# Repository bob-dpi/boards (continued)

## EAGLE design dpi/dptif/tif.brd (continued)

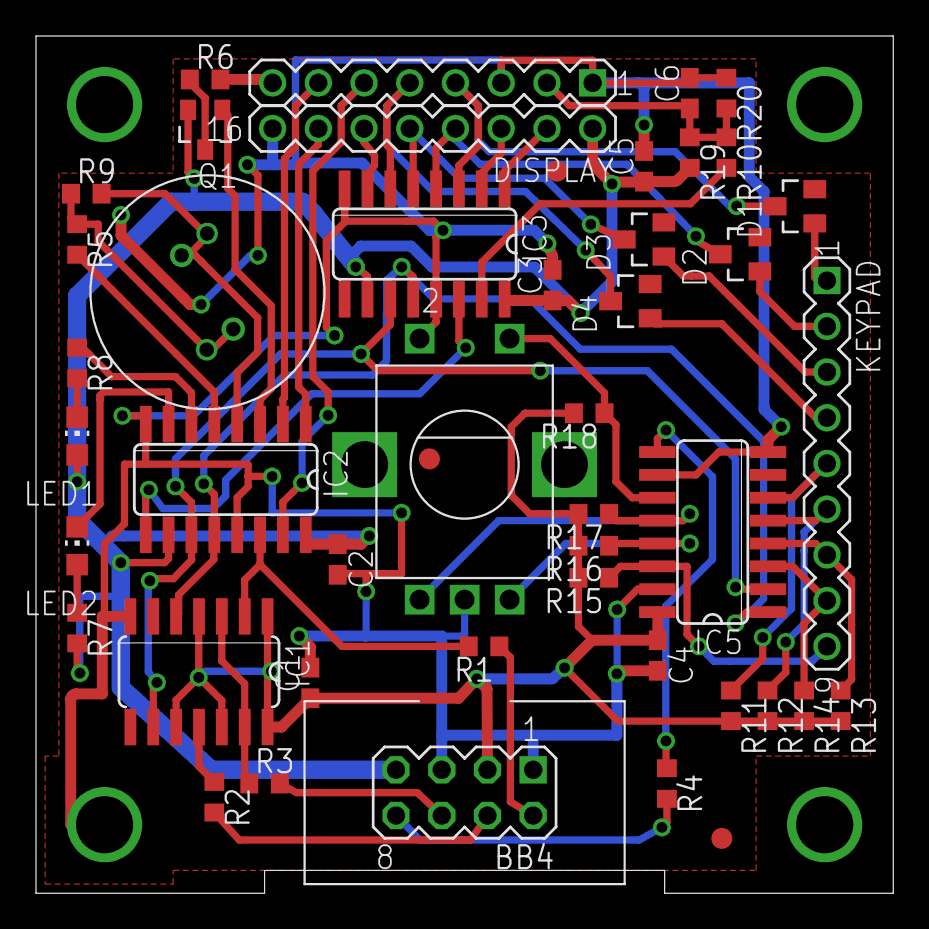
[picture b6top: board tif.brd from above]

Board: 2 copper layers, 47.6 x 47.6 mm, 47 parts (1 on the bottom side), 48 nets.

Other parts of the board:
U$1: DPI-2
U$2, U$3, U$4: FIDUCIAL
